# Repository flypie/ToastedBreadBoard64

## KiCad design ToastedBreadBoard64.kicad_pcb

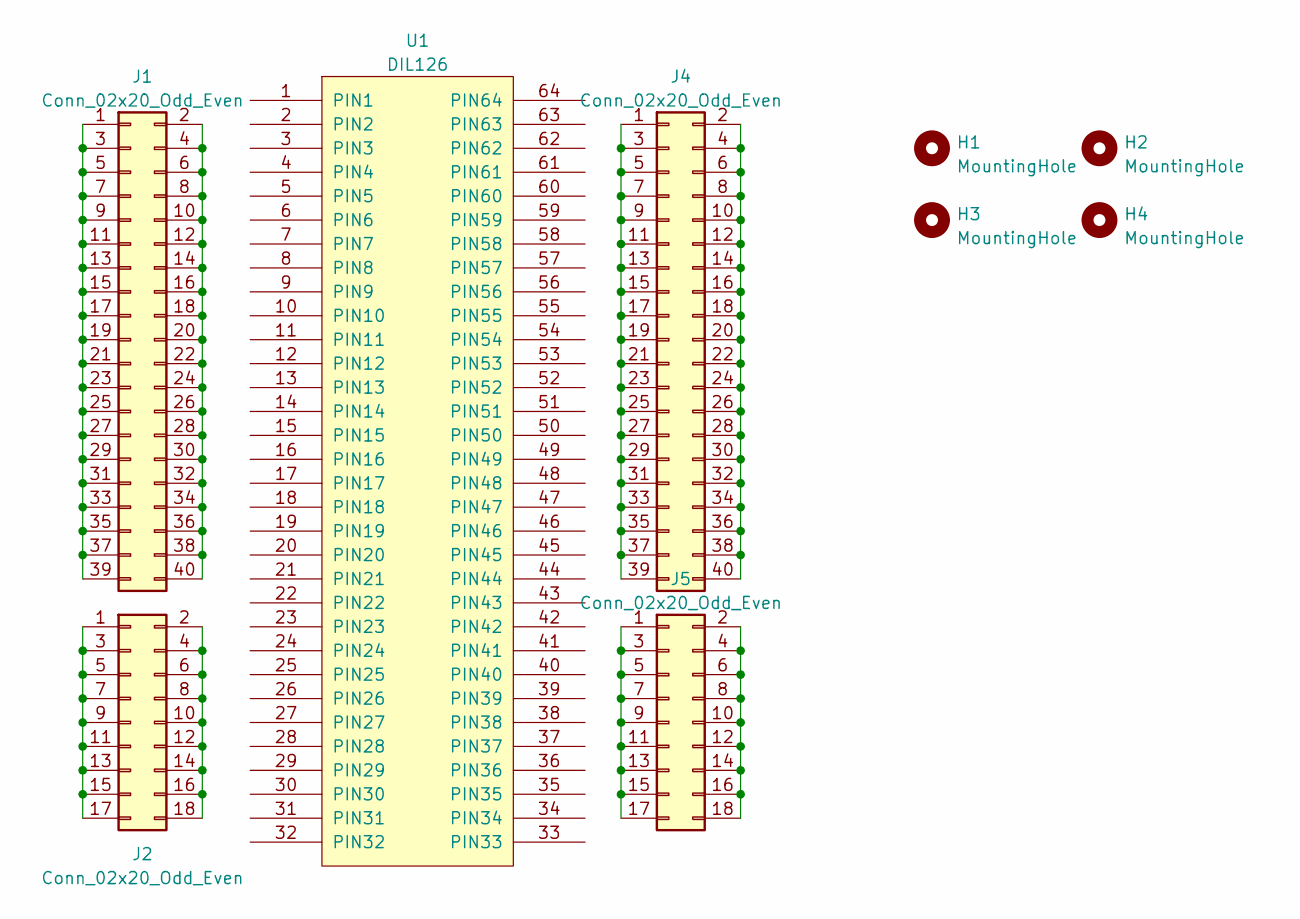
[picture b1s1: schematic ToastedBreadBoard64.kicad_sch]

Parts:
H1, H2, H3, H4: MountingHole; MountingHole_3.5mm_with_Stencil_hole
J1, J4: Conn_02x20_Odd_Even; PinHeader_2x20_P2.54mm_Vertical
J2, J5: Conn_02x20_Odd_Even; PinHeader_2x09_P2.54mm_Vertical
U1: DIL126; DIP-64

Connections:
unnamed: J1.1, J1.3, J1.5, J1.7, J1.9, J1.11, J1.13, J1.15, J1.17, J1.19, J1.21, J1.23, J1.25, J1.27, J1.29, J1.31, J1.33, J1.35, J1.37, J1.39
unnamed: J1.2, J1.4, J1.6, J1.8, J1.10, J1.12, J1.14, J1.16, J1.18, J1.20, J1.22, J1.24, J1.26, J1.28, J1.30, J1.32, J1.34, J1.36, J1.38, J1.40
unnamed: J2.1, J2.3, J2.5, J2.7, J2.9, J2.11, J2.13, J2.15, J2.17
unnamed: J2.2, J2.4, J2.6, J2.8, J2.10, J2.12, J2.14, J2.16, J2.18
unnamed: J4.1, J4.3, J4.5, J4.7, J4.9, J4.11, J4.13, J4.15, J4.17, J4.19, J4.21, J4.23, J4.25, J4.27, J4.29, J4.31, J4.33, J4.35, J4.37, J4.39
unnamed: J4.2, J4.4, J4.6, J4.8, J4.10, J4.12, J4.14, J4.16, J4.18, J4.20, J4.22, J4.24, J4.26, J4.28, J4.30, J4.32, J4.34, J4.36, J4.38, J4.40
unnamed: J5.1, J5.3, J5.5, J5.7, J5.9, J5.11, J5.13, J5.15, J5.17
unnamed: J5.2, J5.4, J5.6, J5.8, J5.10, J5.12, J5.14, J5.16, J5.18

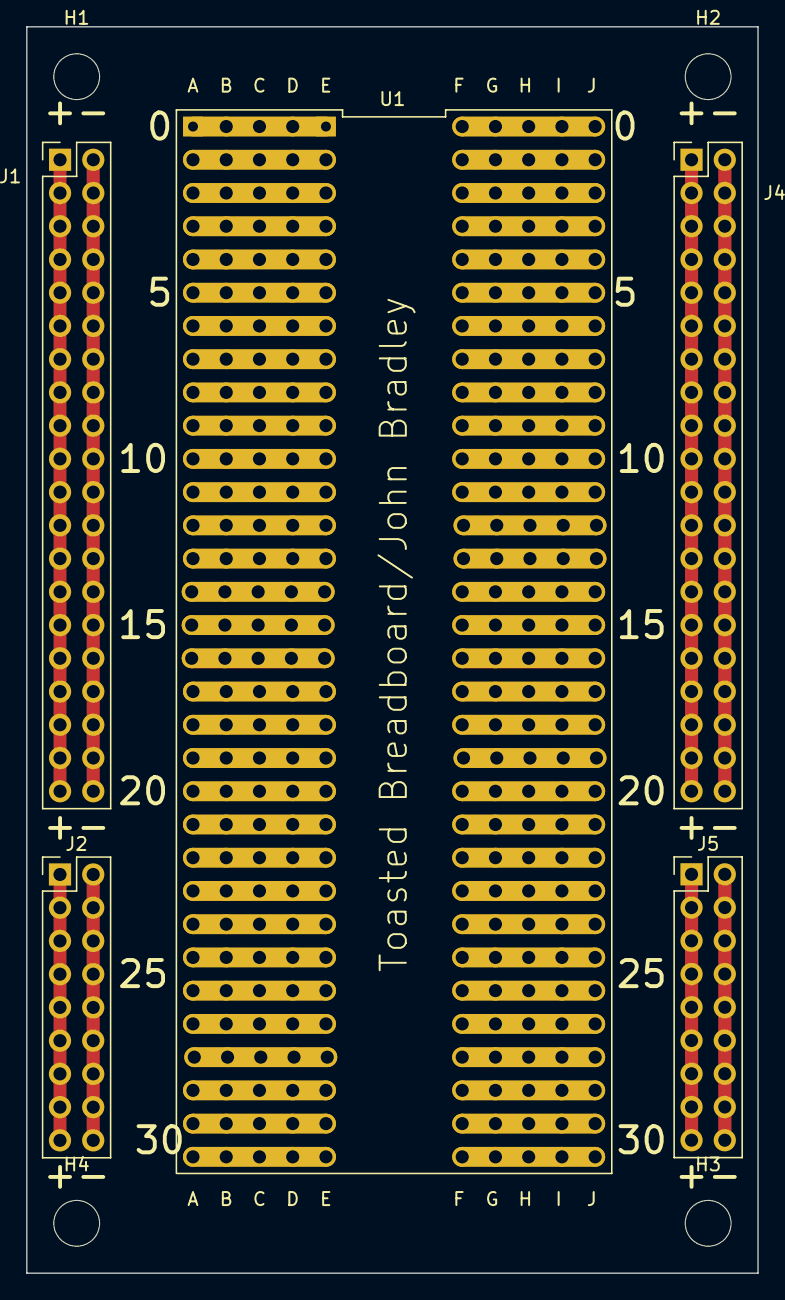
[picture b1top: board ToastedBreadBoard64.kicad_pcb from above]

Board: 2 copper layers, 55.9 x 95.2 mm, 9 parts (0 on the bottom side), 8 nets.

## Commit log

2024-03-13 Remove old backups
2024-03-14 Make all holes the same size.
2024-03-17 Correct width.
